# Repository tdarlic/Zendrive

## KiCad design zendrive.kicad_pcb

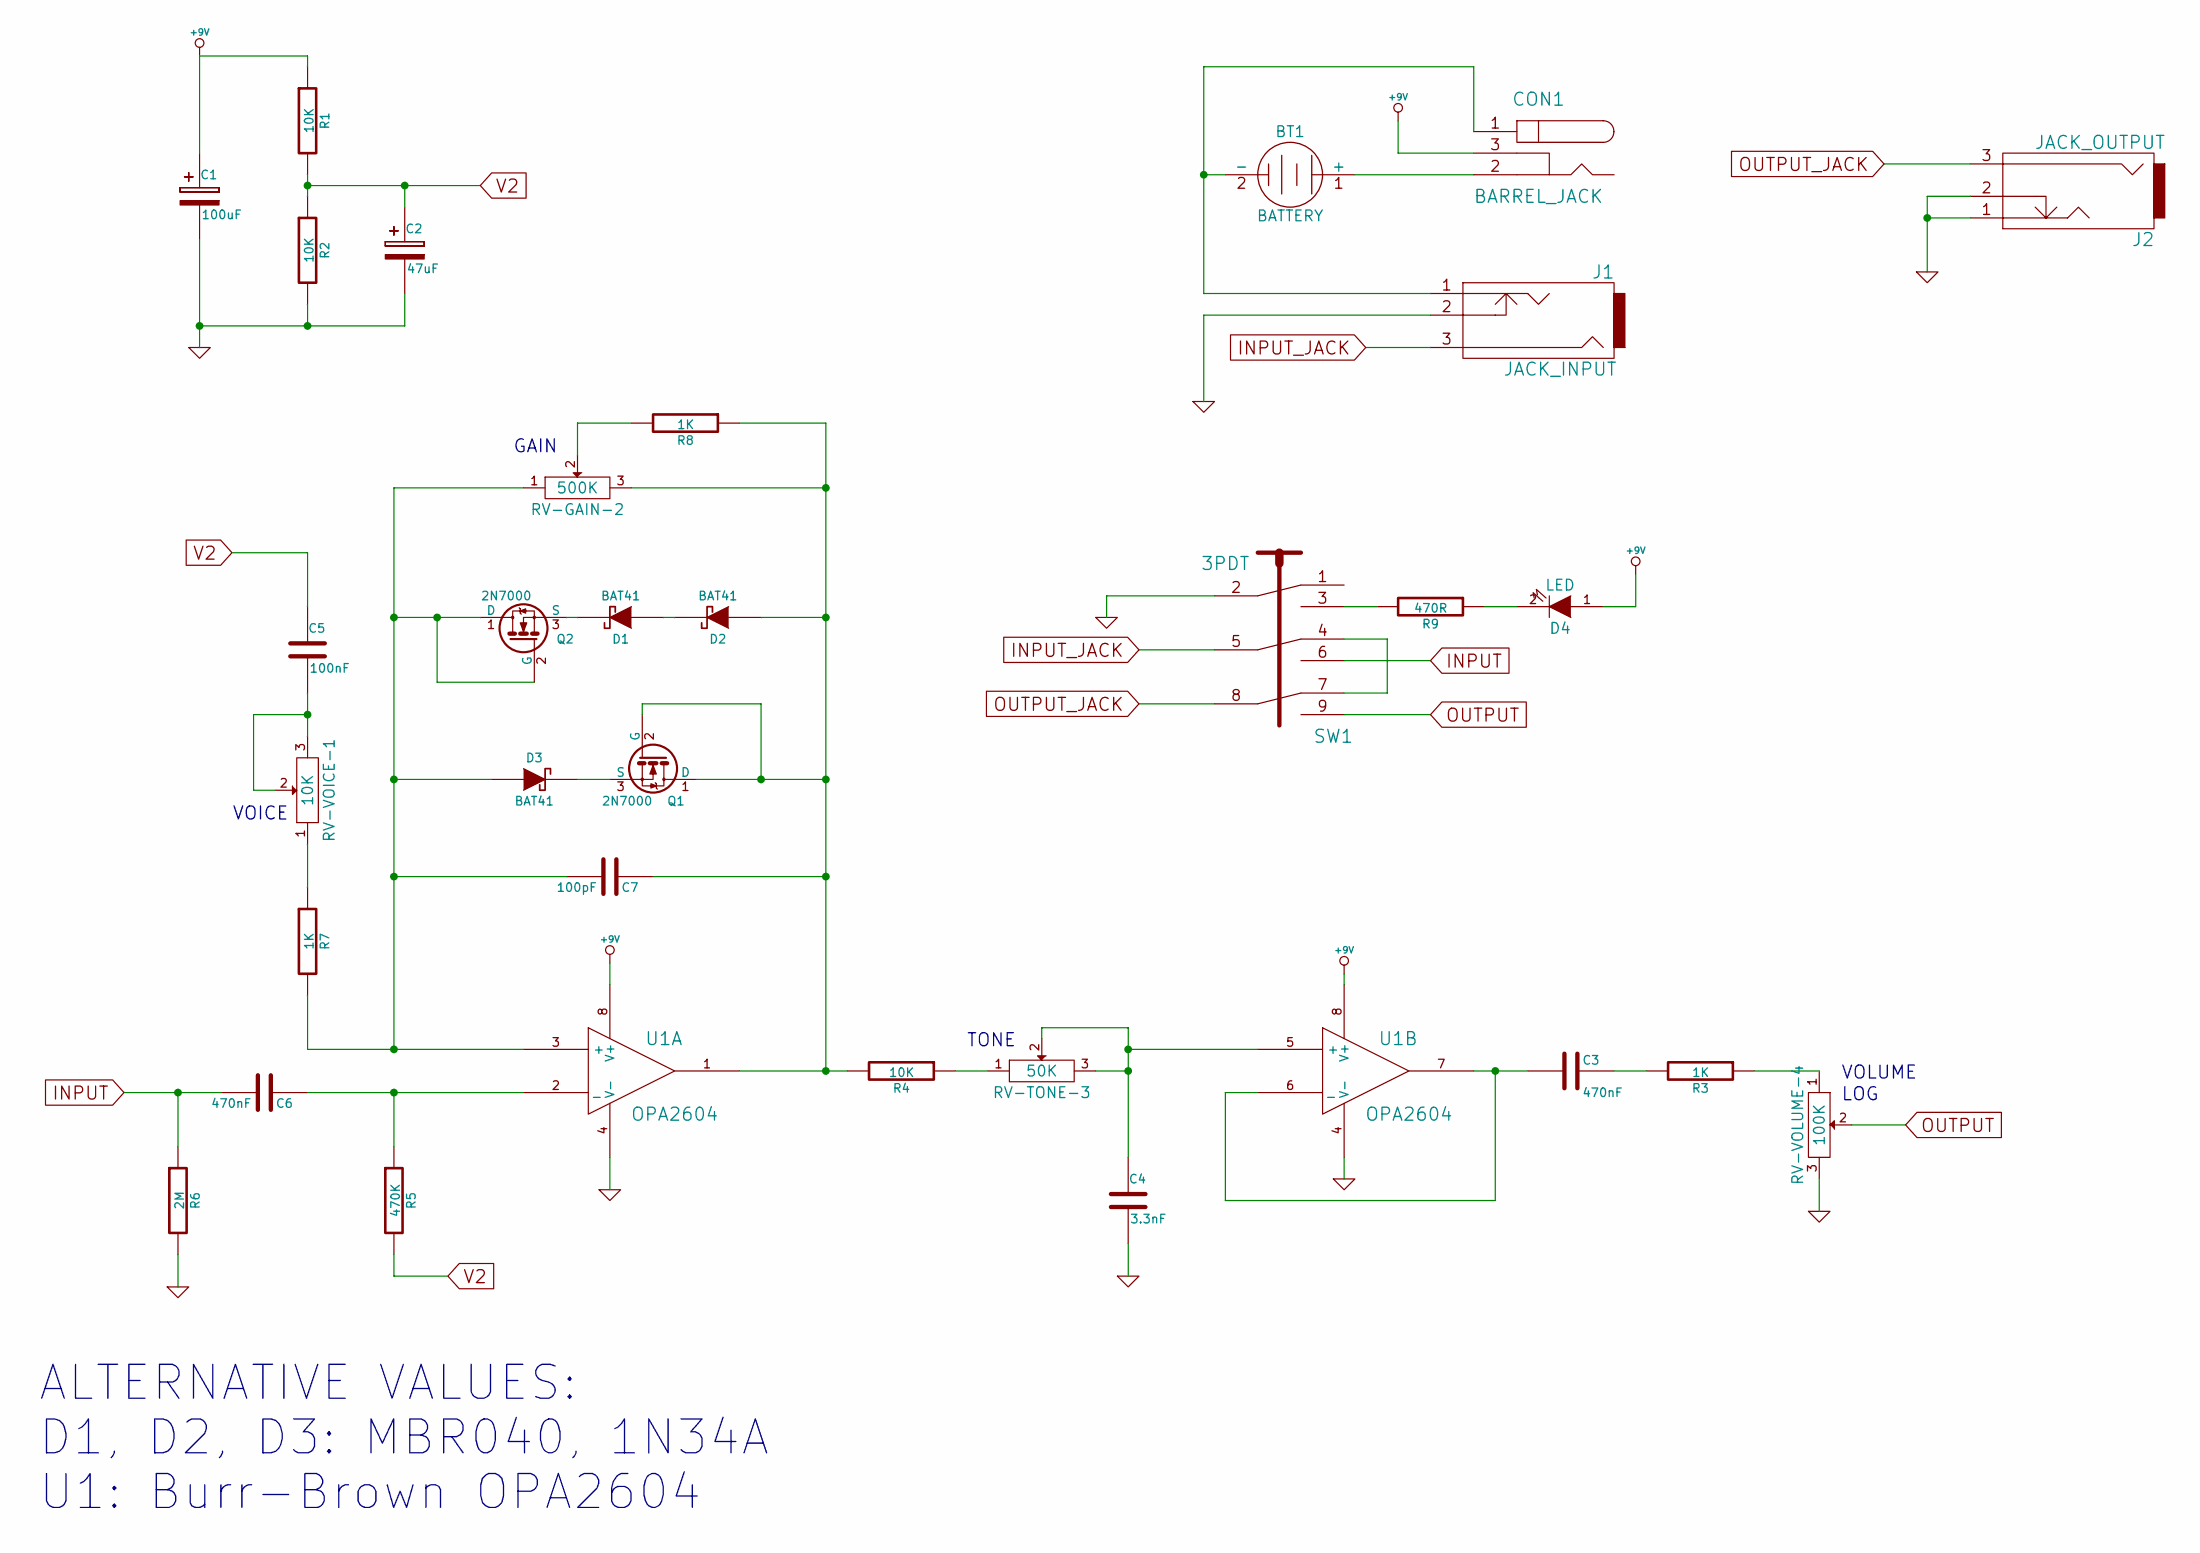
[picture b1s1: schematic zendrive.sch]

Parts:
BT1: BATTERY; Pin_Header_Angled_1x02
C1: 100uF; c_elec_6.3x5.3
C2: 47uF; c_elec_5x5.3
C3, C6: 470nF; Capacitor7.5MMDiscRM5
C4: 3.3nF; Capacitor3MMDiscRM2.5
C5: 100nF; Capacitor7.5MMDiscRM5
C7: 100pF; Capacitor7.5MMDiscRM5
CON1: BARREL_JACK
D1, D2, D3: BAT41; Diode_DO-35_SOD27_Horizontal_RM10
D4: LED; Diode_LED_5mm_round_vertical
J1: JACK_INPUT; NRJ6HF_6MM_ST_JACK
J2: JACK_OUTPUT; NRJ6HF_6MM_ST_JACK
Q1, Q2: 2N7000; TO-92-FET-inline-narrow-oval-SGD
R1, R2, R4: 10K; R_1206_HandSoldering
R3, R7, R8: 1K; R_1206_HandSoldering
R5: 470K; R_1206_HandSoldering
R6: 2M; R_1206_HandSoldering
R9: 470R; R_1206_HandSoldering
RV-GAIN-2: 500K; POT_HEADER_3
RV-TONE-3: 50K; POT_HEADER_3
RV-VOICE-1: 10K; POT_HEADER_3
RV-VOLUME-4: 100K; POT_HEADER_3
SW1: 3PDT
U1: OPA2604; DIP-8__300_ELL

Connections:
+9V: C1.1, CON1.3, D4.1 (A), R1.1, U1.8 (V+)
GND: C1.2, C2.2, C4.2, J1.2, J2.1, J2.2, R2.2, R6.2, RV-VOLUME-4.3, SW1.2, U1.4 (V-)
INPUT: C6.2, R6.1, SW1.6
INPUT_JACK: J1.3, SW1.5
unnamed: BT1.1 (+), CON1.2
unnamed: BT1.2 (-), CON1.1, J1.1
unnamed: C3.1, R3.2
unnamed: C3.2, U1.6 (_), U1.7
unnamed: C4.1, RV-TONE-3.2, RV-TONE-3.3, U1.5 (+)
unnamed: C5.2, RV-VOICE-1.2, RV-VOICE-1.3
unnamed: C6.1, R5.1, U1.2 (_)
unnamed: C7.1, D2.1 (A), Q1.1 (D), Q1.2 (G), R4.2, R8.1, RV-GAIN-2.3, U1.1
unnamed: C7.2, D3.1 (A), Q2.1 (D), Q2.2 (G), R7.2, RV-GAIN-2.1, U1.3 (+)
unnamed: D1.1 (A), D2.2 (K)
unnamed: D1.2 (K), Q2.3 (S)
unnamed: D3.2 (K), Q1.3 (S)
unnamed: D4.2 (K), R9.1
unnamed: R3.1, RV-VOLUME-4.1
unnamed: R4.1, RV-TONE-3.1
unnamed: R7.1, RV-VOICE-1.1
unnamed: R8.2, RV-GAIN-2.2
unnamed: R9.2, SW1.3
unnamed: SW1.4, SW1.7
OUTPUT: RV-VOLUME-4.2, SW1.9
OUTPUT_JACK: J2.3, SW1.8
V2: C2.1, C5.1, R1.2, R2.1, R5.2

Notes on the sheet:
GAIN
VOICE
TONE
VOLUME
LOG
ALTERNATIVE VALUES: D1, D2, D3: MBR040, 1N34A U1: Burr-Brown OPA2604

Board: 2 copper layers, 32 parts (11 on the bottom side), 26 nets, no tracks yet.

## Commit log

2015-01-07 :neckbeard: Added .gitattributes & .gitignore files
2015-01-07 Zendrive
    Zendrive Kicad Files
2015-01-07 Deleted Zdrive01.sch
2015-01-07 Board complete
2015-01-07 Added pot connections
2015-01-07 REMOVED POT CONN
2015-01-07 Adding footprints
2015-01-10 Adding PCB
2015-01-10 Adding ignore folder
